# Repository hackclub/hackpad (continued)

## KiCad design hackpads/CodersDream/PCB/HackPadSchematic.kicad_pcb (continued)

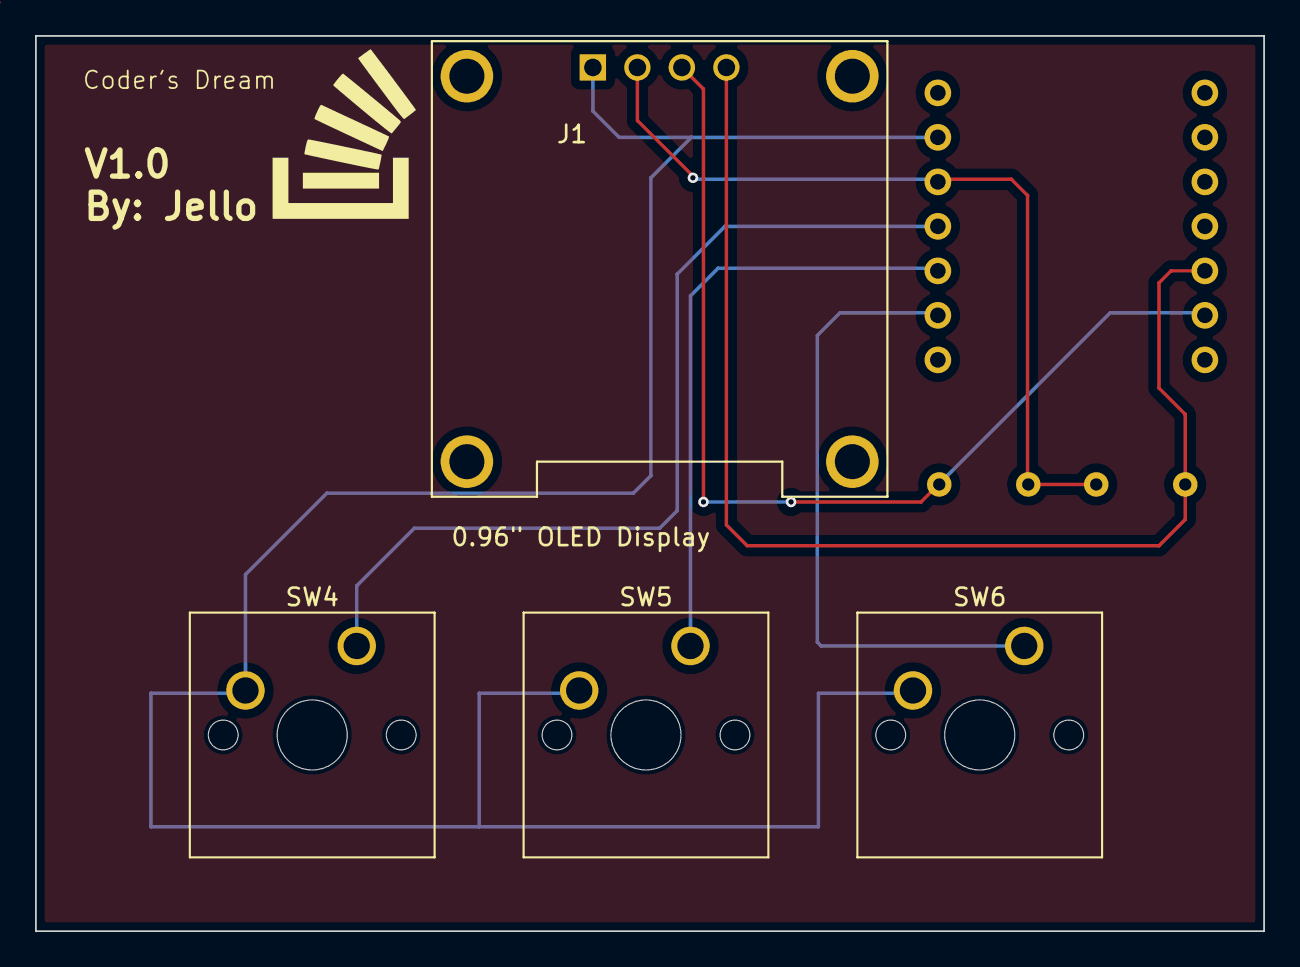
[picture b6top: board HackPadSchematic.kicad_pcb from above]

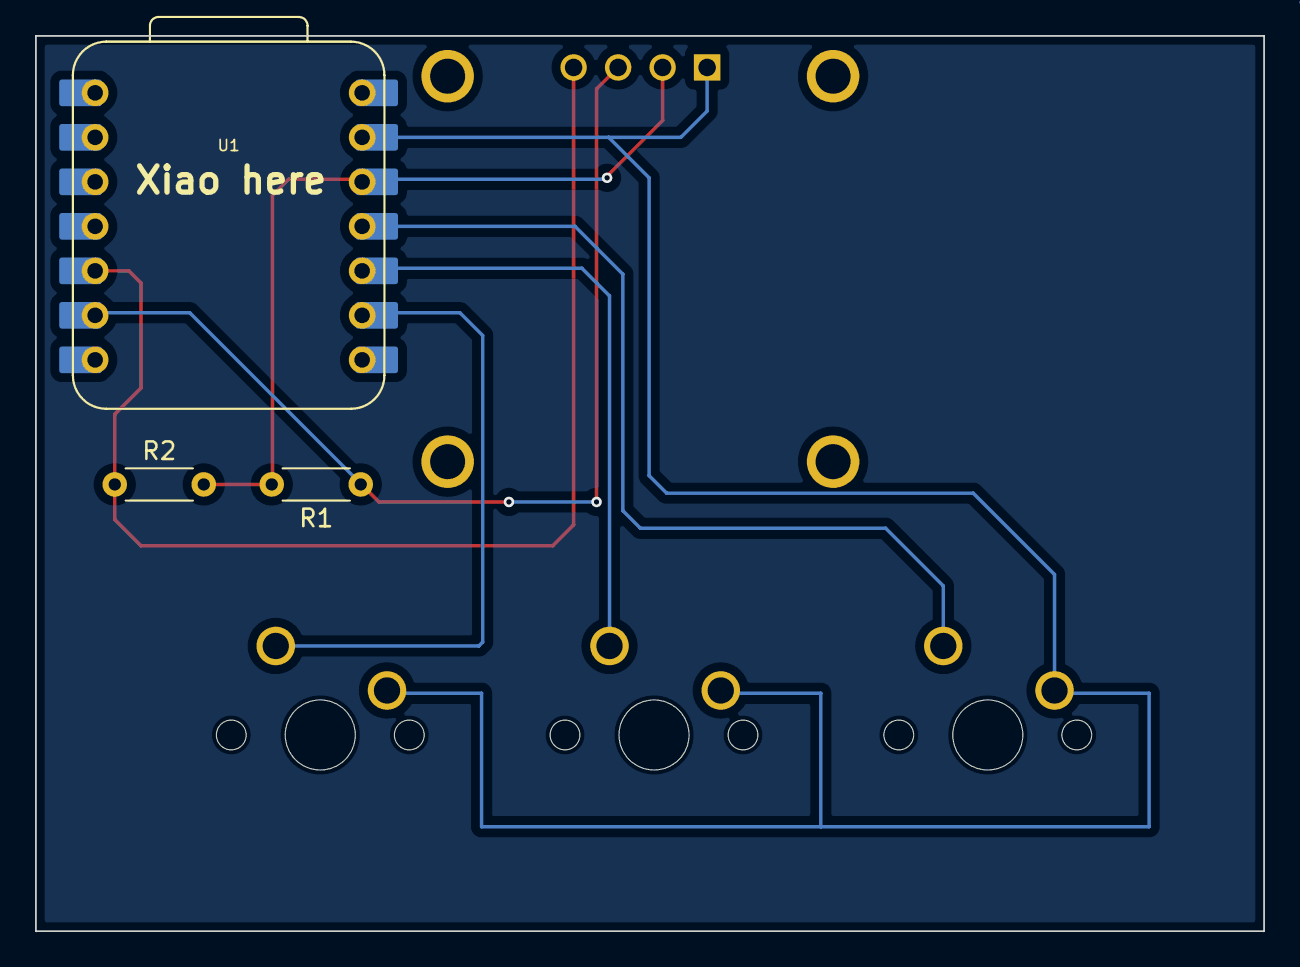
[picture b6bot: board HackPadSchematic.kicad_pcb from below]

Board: 2 copper layers, 70.1 x 51.1 mm, 7 parts (3 on the bottom side), 7 nets.

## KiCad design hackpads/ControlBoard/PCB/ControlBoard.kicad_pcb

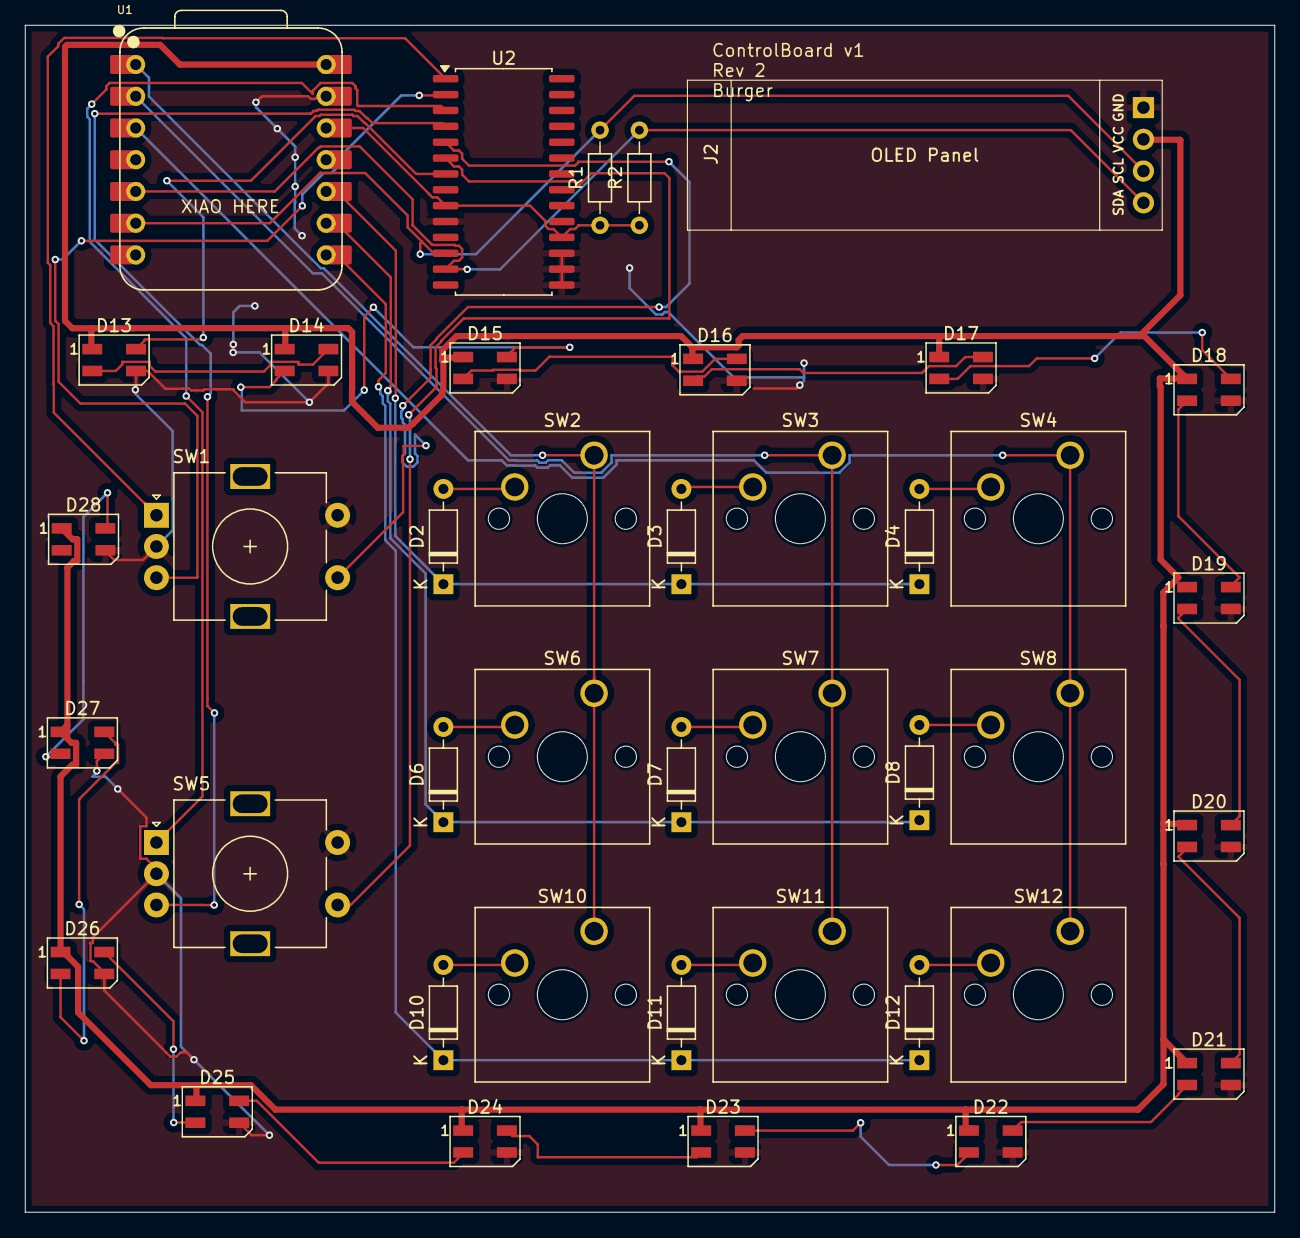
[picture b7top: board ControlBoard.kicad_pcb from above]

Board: 2 copper layers, 100.0 x 95.0 mm, 41 parts (0 on the bottom side), 42 nets.

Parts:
D2, D3, D4, D6, D7, D8, D10, D11, D12: D; D_DO-35_SOD27_P7.62mm_Horizontal
D13, D14, D15, D16, D17, D18, D19, D20, D21, D22, D23, D24, D25, D26, D27, D28: WS2812B; LED_SK6812MINI_PLCC4_3.5x3.5mm_P1.75mm
J2: OLED_128x32; SSD1306-0.91-OLED-4pin-128x32
R1, R2: R; R_Axial_DIN0204_L3.6mm_D1.6mm_P7.62mm_Horizontal
SW1, SW5: RotaryEncoder_Switch; RotaryEncoder_Alps_EC11E-Switch_Vertical_H20mm
SW2, SW3, SW4, SW6, SW7, SW8, SW10, SW11, SW12: SW_Push; SW_Cherry_MX_1.00u_PCB
U1: XIAO-RP2040-DIP
U2: MCP23017_SO; SOIC-28W_7.5x17.9mm_P1.27mm

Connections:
+3.3V: R1.1, R2.1, U1.12 (3V3), U2.9 (VDD), U2.18 (~RESET)
+5V: D13.1 (VDD), D14.1 (VDD), D15.1 (VDD), D16.1 (VDD), D17.1 (VDD), D18.1 (VDD), D19.1 (VDD), D20.1 (VDD), D21.1 (VDD), D22.1 (VDD), D23.1 (VDD), D24.1 (VDD), D25.1 (VDD), D26.1 (VDD), D27.1 (VDD), D28.1 (VDD), J2.2 (VCC), U1.14 (VBUS)
COL1: SW2.1, SW6.1, SW10.1, U1.1 (GPIO26/ADC0/A0)
COL2: SW3.1, SW7.1, SW11.1, U1.2 (GPIO27/ADC1/A1)
COL3: SW4.1, SW8.1, SW12.1, U1.3 (GPIO28/ADC2/A2)
GND: D13.3 (VSS), D14.3 (VSS), D15.3 (VSS), D16.3 (VSS), D17.3 (VSS), D18.3 (VSS), D19.3 (VSS), D20.3 (VSS), D21.3 (VSS), D22.3 (VSS), D23.3 (VSS), D24.3 (VSS), D25.3 (VSS), D26.3 (VSS), D27.3 (VSS), D28.3 (VSS), J2.1 (GND), SW1.C, SW1.S2, SW5.C, SW5.S2, U1.13 (GND), U2.10 (VSS), U2.15 (A0), U2.16 (A1), U2.17 (A2)
unnamed: D2.2 (A), SW2.2
unnamed: D3.2 (A), SW3.2
unnamed: D4.2 (A), SW4.2
unnamed: D6.2 (A), SW6.2
unnamed: D7.2 (A), SW7.2
unnamed: D8.2 (A), SW8.2
unnamed: D10.2 (A), SW10.2
unnamed: D11.2 (A), SW11.2
unnamed: D12.2 (A), SW12.2
unnamed: D13.4 (DIN), U2.7 (GPB6)
unnamed: D13.2 (DOUT), D14.4 (DIN)
unnamed: D14.2 (DOUT), D15.4 (DIN)
unnamed: D15.2 (DOUT), D16.4 (DIN)
unnamed: D16.2 (DOUT), D17.4 (DIN)
unnamed: D17.2 (DOUT), D18.4 (DIN)
unnamed: D18.2 (DOUT), D19.4 (DIN)
unnamed: D19.2 (DOUT), D20.4 (DIN)
unnamed: D20.2 (DOUT), D21.4 (DIN)
unnamed: D21.2 (DOUT), D22.4 (DIN)
unnamed: D22.2 (DOUT), D23.4 (DIN)
unnamed: D23.2 (DOUT), D24.4 (DIN)
unnamed: D24.2 (DOUT), D25.4 (DIN)
unnamed: D25.2 (DOUT), D26.4 (DIN)
unnamed: D26.2 (DOUT), D27.4 (DIN)
unnamed: D27.2 (DOUT), D28.4 (DIN)
unnamed: J2.3 (SCL), R1.2, U1.6 (GPIO7/SCL), U2.12 (SCK)
unnamed: J2.4 (SDA), R2.2, U1.5 (GPIO6/SDA), U2.13 (SDA)
unnamed: SW1.A, U2.1 (GPB0)
unnamed: SW1.B, U2.2 (GPB1)
unnamed: SW5.A, U2.3 (GPB2)
unnamed: SW5.B, U2.4 (GPB3)
unnamed: SW1.S1, U2.5 (GPB4)
unnamed: SW5.S1, U2.6 (GPB5)
ROW1: D2.1 (K), D3.1 (K), D4.1 (K), U1.10 (GPIO4/MISO)
ROW2: D6.1 (K), D7.1 (K), D8.1 (K), U1.9 (GPIO2/SCK)
ROW3: D10.1 (K), D11.1 (K), D12.1 (K), U1.8 (GPIO1/RX)

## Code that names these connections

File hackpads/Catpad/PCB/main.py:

import board
import busio
from kmk.kmk_keyboard import KMKKeyboard
from kmk.keys import KC
from kmk.scanners import DiodeOrientation
from kmk.extensions.display import Display, TextEntry
from kmk.extensions.display.ssd1306 import SSD1306

# Define column and row pins for a 4x5 matrix
COL1 = board.D2
COL2 = board.D3
COL3 = board.D4
COL4 = board.D5
ROW1 = board.D6
ROW2 = board.D7
ROW3 = board.D8
ROW4 = board.D9
ROW5 = board.D10

# Initialize I2C bus for the displays
i2c_bus = busio.I2C(board.D4, board.D5)

# Initialize the SSD1306 displays
display_driver1 = SSD1306(
    i2c=i2c_bus,
    device_address=0x3C,  # First OLED address
)

display_driver2 = SSD1306(
    i2c=i2c_bus,
    device_address=0x3D,  # Second OLED address
)

# Create the keyboard instance
keyboard = KMKKeyboard()

# Define column and row pins
keyboard.col_pins = (COL1, COL2, COL3, COL4)
keyboard.row_pins = (ROW1, ROW2, ROW3, ROW4, ROW5)
keyboard.diode_orientation = DiodeOrientation.COL2ROW

# Set up the displays with initial text
display1 = Display(
    display=display_driver1,
    entries=[TextEntry(text='Name', x=0, y=0, y_anchor='M')],
    width=128,
    height=32,
    dim_time=10,
    dim_target=0.2,
    off_time=1200,
    brightness=1,
)

display2 = Display(
    display=display_driver2,
    entries=[TextEntry(text='WELCOME', x=0, y=0, y_anchor='M')],
    width=128,
    height=32,
    dim_time=10,
    dim_target=0.2,
    off_time=1200,
    brightness=1,
)

# Add displays to keyboard extensions
keyboard.extensions.append(display1)
keyboard.extensions.append(display2)

# Define the keymap
keyboard.keymap = [
    [KC.MPRV, KC.MNXT, KC.NO, KC.NO],  # Row 1
    [KC.NO,   KC.NO,   KC.NO, KC.NO],  # Row 2
    [KC.NO,   KC.Z,    KC.X,  KC.NO],  # Row 3
    [KC.NO,   KC.NO,   KC.NO, KC.NO],  # Row 4
    [KC.NO,   KC.NO,   KC.NO, KC.NO],  # Row 5
]

# Start the keyboard
if __name__ == '__main__':
    keyboard.go()
